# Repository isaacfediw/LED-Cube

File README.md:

# LED-Cube
This is a personal project I made alone which is an LED cube with RGB LED matrixes on 4 sides, which can be programmed in any way

## Hardware
The hardware consists of an arduino nano, and 4 16x16 RGB LED matrixes  

## Software
To design the box, I used Fusion 360  
To program the arduino I used VSCode with the PlatformIO plugin in C++  
Recently I also added a custom pixel art editor which I made using Java, which allows you to make your own pixel art and display it on the LED cube  

## 3D Design
To make my design easily printable, and to reduce the amount of wasted filament when prints inevitably had oversights I made the design consist of a base, 4 walls, and a roof. The walls friction fit into the base, and the LED matrix sandwiches between the wall and the matrix's front cover. The front covers insert into the walls with 3D printed pegs. I went for this design because I didn't want there to be visible screws in the white cover  

## Pictures
### Display

### 3D Model

### Wiring

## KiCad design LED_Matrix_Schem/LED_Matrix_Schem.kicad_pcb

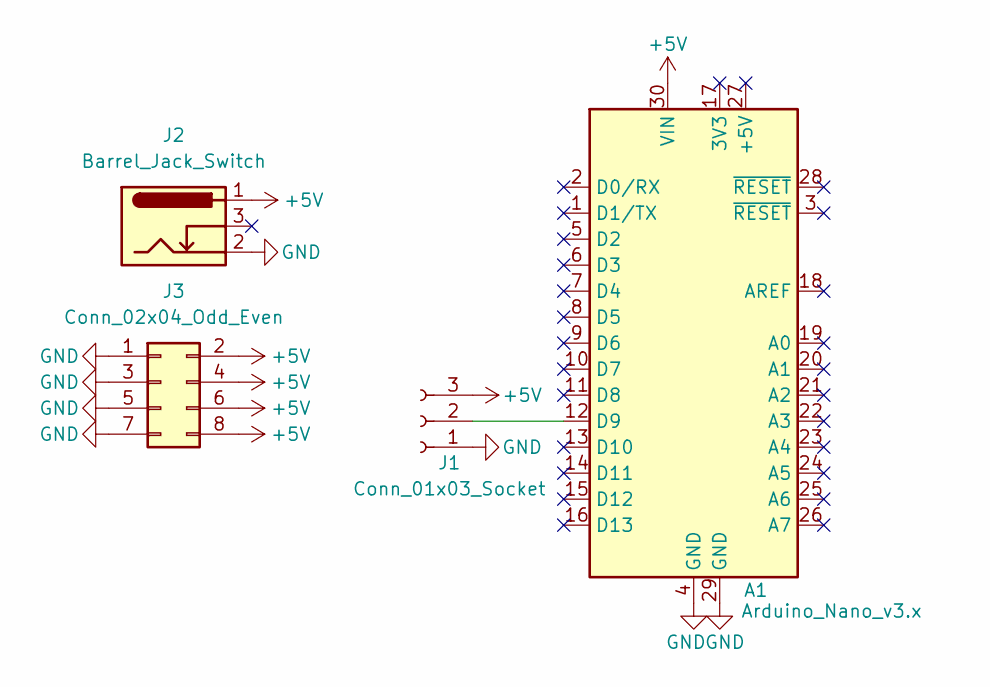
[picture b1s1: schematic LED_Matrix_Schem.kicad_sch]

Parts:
A1: Arduino_Nano_v3.x; Arduino_Nano
J1: Conn_01x03_Socket; PinSocket_1x03_P2.54mm_Vertical
J2: Barrel_Jack_Switch; BarrelJack_Horizontal
J3: Conn_02x04_Odd_Even; PinSocket_2x04_P2.54mm_Vertical

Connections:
+5V: A1.30 (VIN), J1.3, J2.1, J3.2, J3.4, J3.6, J3.8
GND: A1.4 (GND), A1.29 (GND), J1.1, J2.2, J3.1, J3.3, J3.5, J3.7
unnamed: A1.12 (D9), J1.2

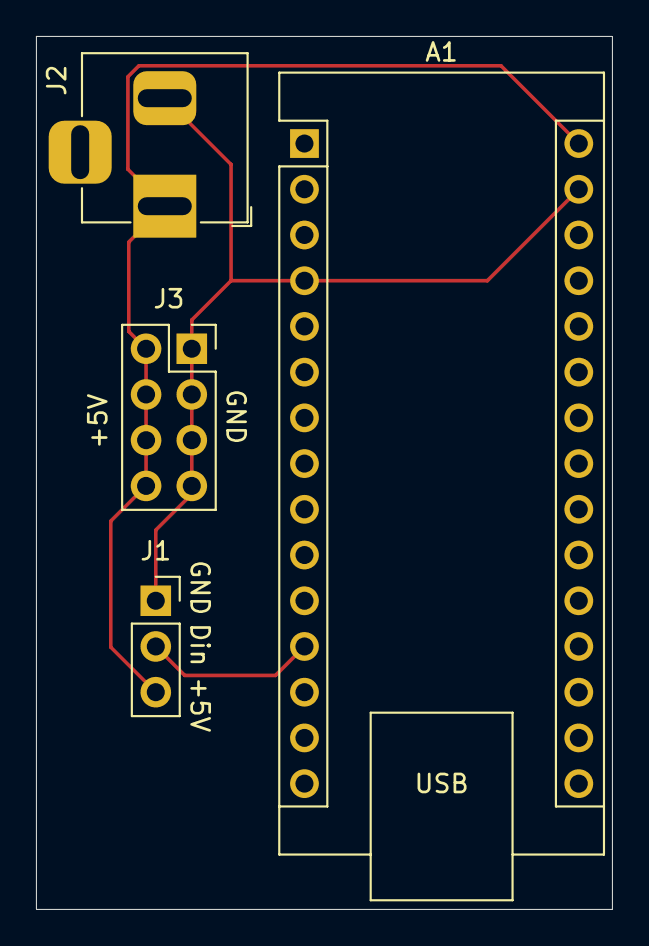
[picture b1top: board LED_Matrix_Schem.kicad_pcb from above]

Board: 2 copper layers, 32.0 x 48.5 mm, 4 parts (0 on the bottom side), 3 nets.

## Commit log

2026-01-15 Expand README with project details
    Added sections for hardware, software, and 3D design details.
2026-01-15 Fix typo in README regarding programming language
2026-01-15 Rename Led+Matrix+Cube+V2.stl to Led Matrix Cube.stl
2026-05-06 Add new image to README display section
    Added a new image to the display section of the README.
2026-05-06 Update README with custom pixel art editor details
    Added information about a custom pixel art editor created in Java.
